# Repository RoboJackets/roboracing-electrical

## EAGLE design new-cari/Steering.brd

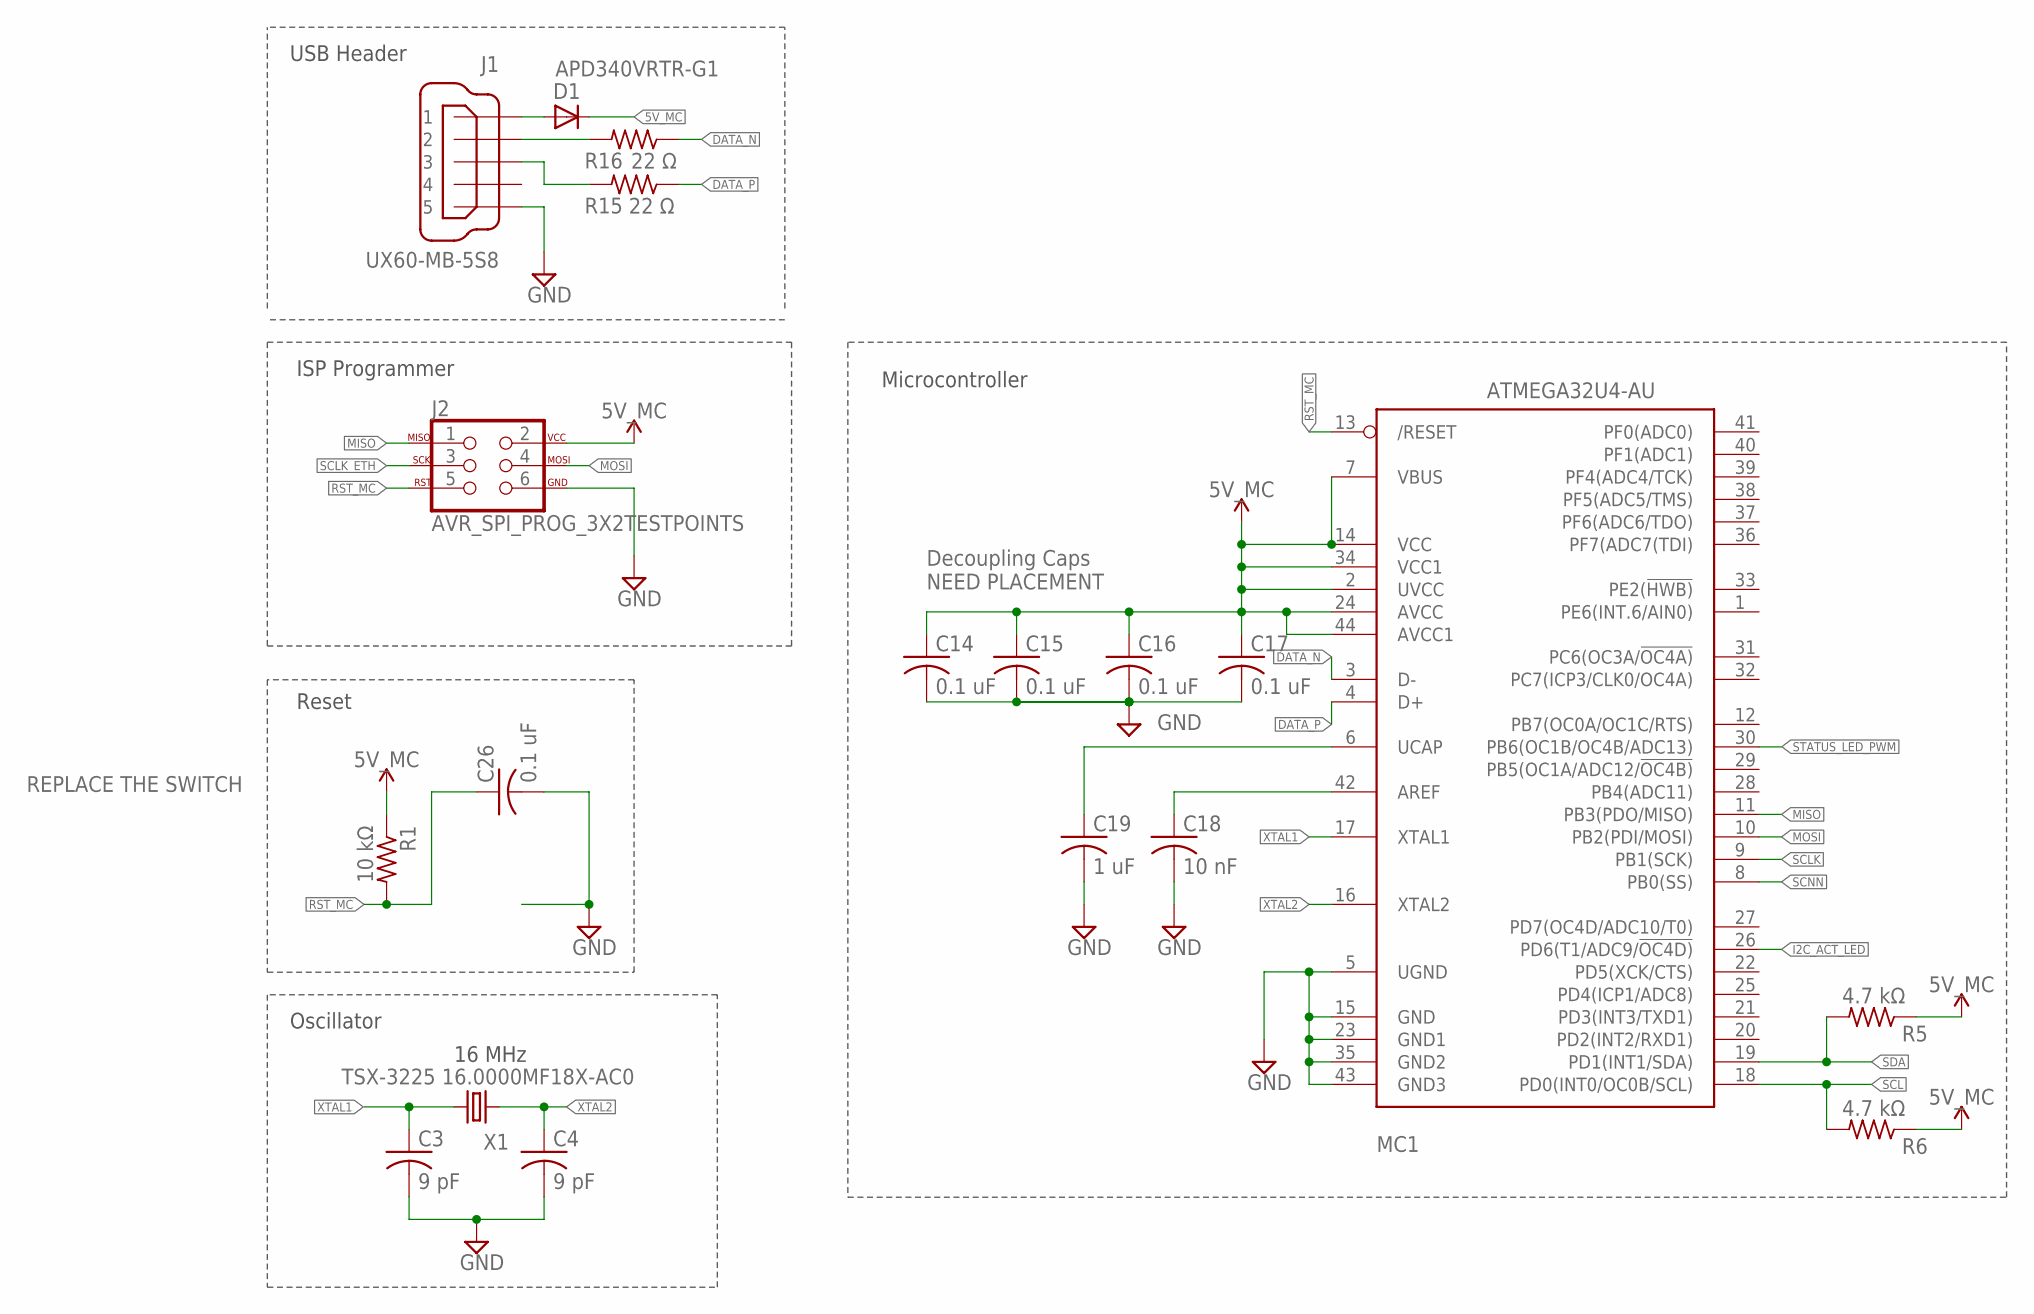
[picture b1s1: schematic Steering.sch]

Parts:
C3, C4: 9 pF; C0603
C14, C15, C16, C17, C26: 0.1 uF; C0603
C18: 10 nF; C0603
C19: 1 uF; C0603
D1: APD340VRTR-G1; DO-214AC
J1: UX60-MB-5S8
J2: AVR_SPI_PROG_3X2TESTPOINTS; 2X3_TEST_POINTS
MC1: ATMEGA32U4-AU; TQFP44
R1: 10 kΩ; R0603
R5, R6: 4.7 kΩ; R0603
R15, R16: 22 Ω; R0603
X1: TSX-3225 16.0000MF18X-AC0; XTAL-3.2X2.5

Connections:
5V_MC: C14.1, C15.1, C16.1, C17.1, D1.C, J2.2, MC1.2 (UVCC), MC1.7 (VBUS), MC1.14 (VCC), MC1.24 (AVCC), MC1.34 (VCC1), MC1.44 (AVCC1), R1.1, R5.1, R6.1
AREF: C18.1, MC1.42 (AREF)
DATA_N: MC1.3 (D-), R16.1
DATA_P: MC1.4 (D+), R15.1
GND: C3.2, C4.2, C14.2, C15.2, C16.2, C17.2, C18.2, C19.2, C26.2, J1.5, J2.6, MC1.5 (UGND), MC1.15 (GND), MC1.23 (GND1), MC1.35 (GND2), MC1.43 (GND3)
I2C_ACT_LED: MC1.26 (PD6(T1/ADC9/!OC4D))
MISO: J2.1, MC1.11 (PB3(PDO/MISO))
MOSI: J2.4, MC1.10 (PB2(PDI/MOSI))
unnamed: D1.A, J1.1
unnamed: J1.2, R16.2
unnamed: J1.3, R15.2
RST_MC: C26.1, J2.5, MC1.13 (/RESET), R1.2
SCL: MC1.18 (PD0(INT0/OC0B/SCL)), R6.2
SCLK: MC1.9 (PB1(SCK))
SCLK_ETH: J2.3
SCNN: MC1.8 (PB0(SS))
SDA: MC1.19 (PD1(INT1/SDA)), R5.2
STATUS_LED_PWM: MC1.30 (PB6(OC1B/OC4B/ADC13))
UCAP: C19.1, MC1.6 (UCAP)
XTAL1: C3.1, MC1.17 (XTAL1), X1.1
XTAL2: C4.1, MC1.16 (XTAL2), X1.3 (2)

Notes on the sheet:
Reset
Oscillator
Microcontroller
USB Header
16 MHz
ISP Programmer
Decoupling Caps NEED PLACEMENT
REPLACE THE SWITCH

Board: 2 copper layers, 19 parts (15 on the bottom side), 16 nets, no tracks yet.

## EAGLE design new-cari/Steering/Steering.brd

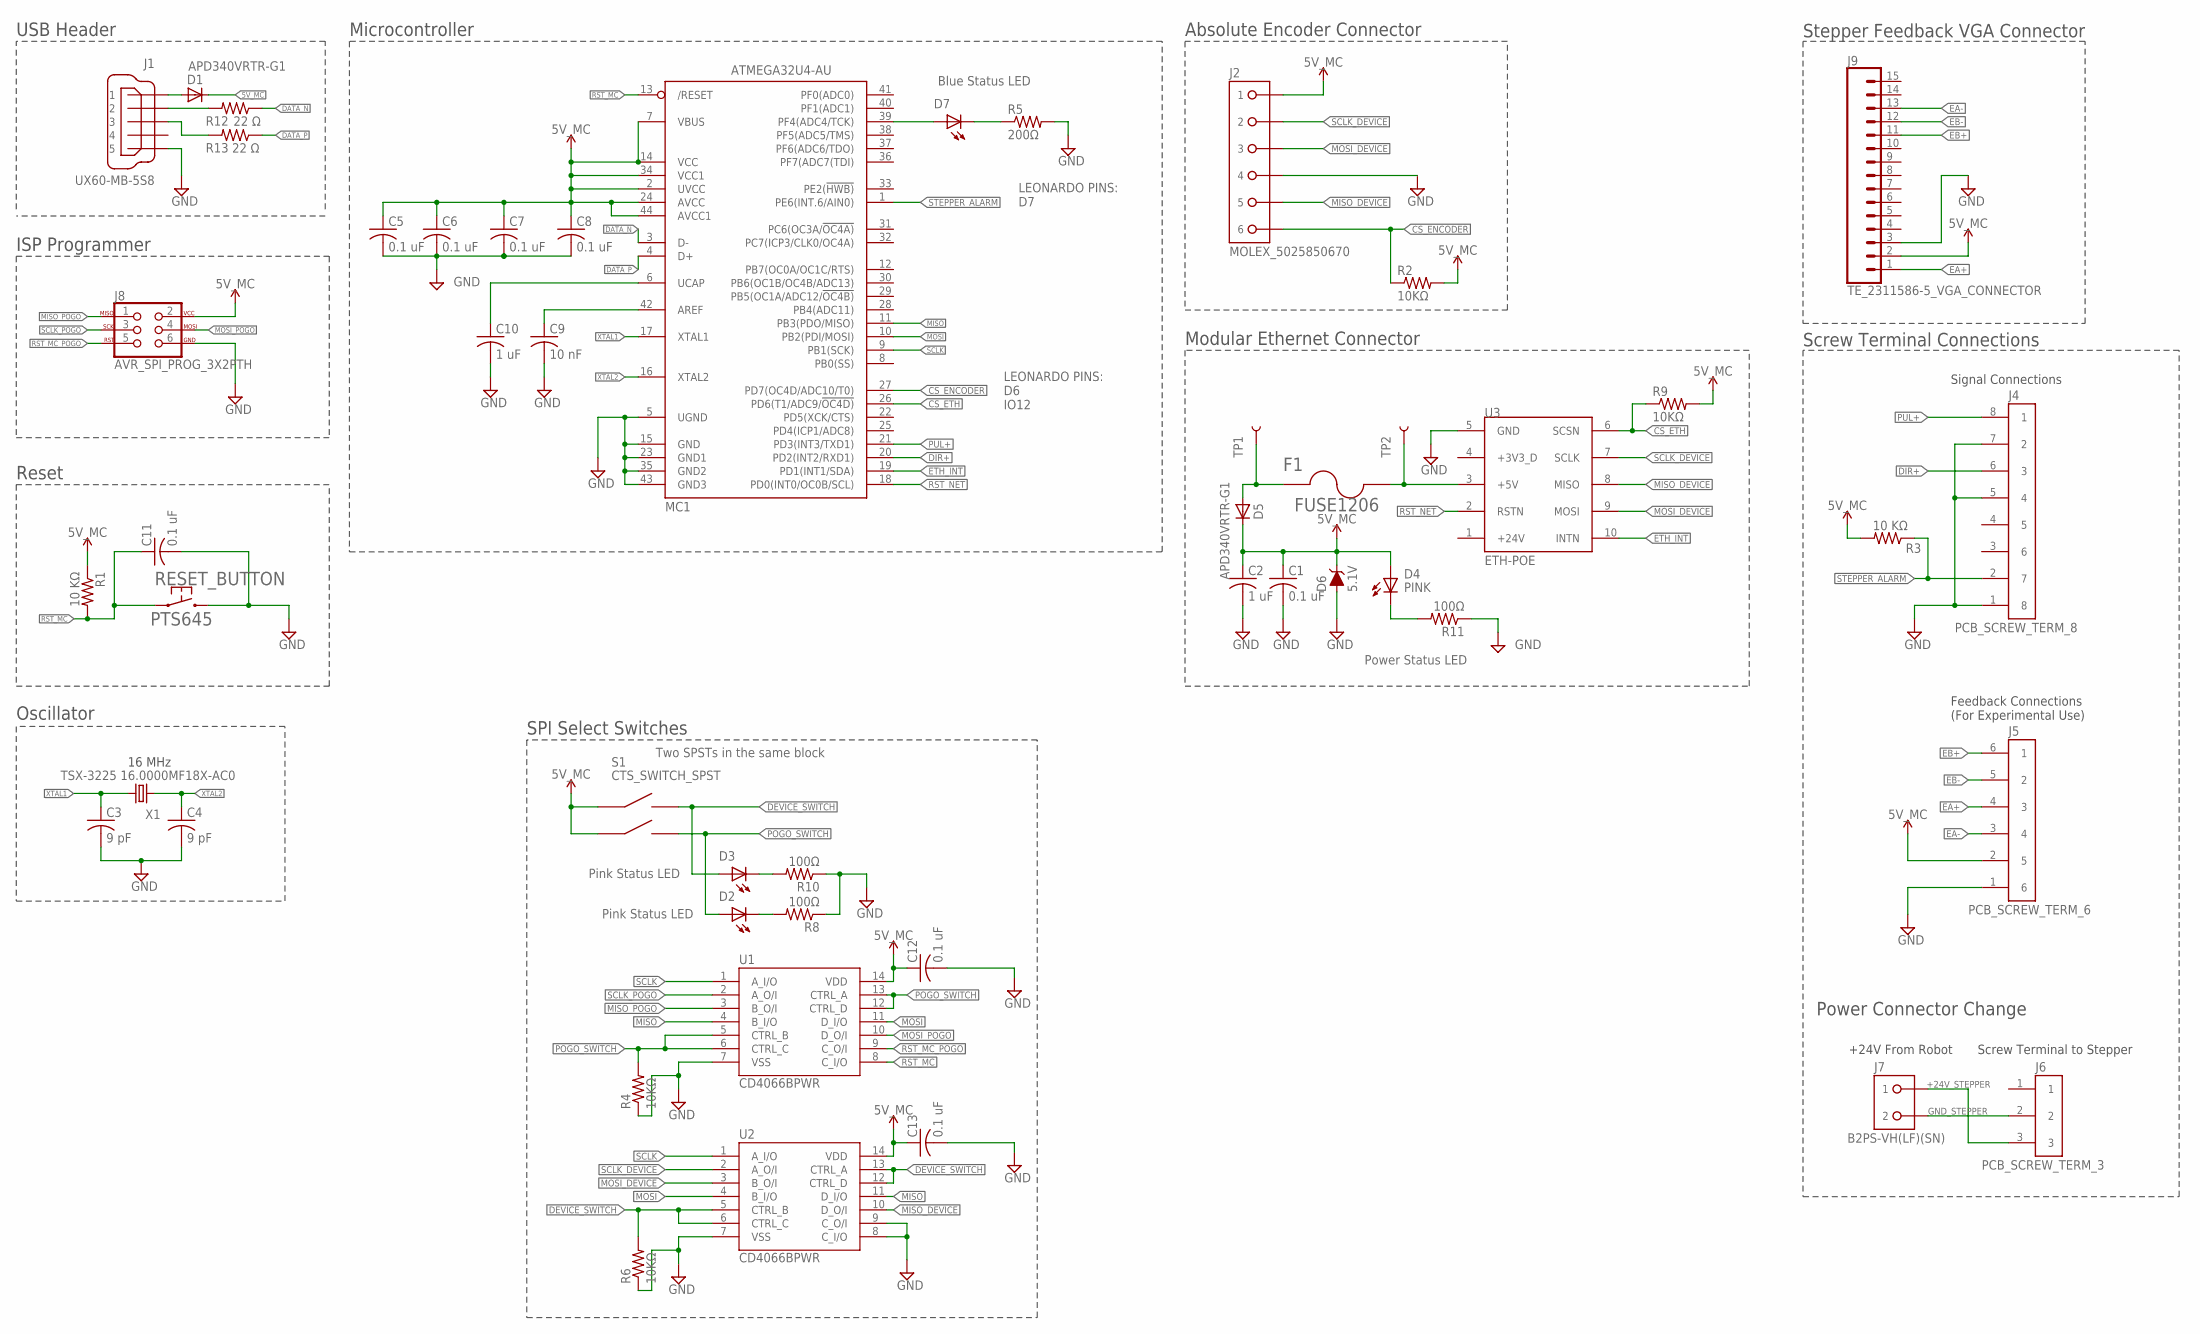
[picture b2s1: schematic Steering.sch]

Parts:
C1, C5, C6, C7, C8, C11, C12, C13: 0.1 uF; C0603
C2, C10: 1 uF; C0603
C3, C4: 9 pF; C0603
C9: 10 nF; C0603
D1, D5: APD340VRTR-G1; DO-214AC
D2, D3: LED_AA3528VRVCS/A; KINGBRIGHT_LED
D4: PINK; KINGBRIGHT_LED
D6: 5.1V; SOD-323
D7: BLUE; CHIP-LED0603
F1: FUSE1206; F1206
J1: UX60-MB-5S8
J2: MOLEX_5025850670
J4: PCB_SCREW_TERM_8; SCREW_TERMINAL_PCB_CONN_8_POLE
J5: PCB_SCREW_TERM_6; SCREW_TERMINAL_PCB_CONN_6_POLE
J6: PCB_SCREW_TERM_3; SCREW_TERMINAL_PCB_CONN_3_POLE
J7: B2PS-VH(LF)(SN); B2PS-CENTERED
J8: AVR_SPI_PROG_3X2PTH; 2X3
J9: TE_2311586-5_VGA_CONNECTOR; TE_VGA_2311586-5
MC1: ATMEGA32U4-AU; TQFP44
R1, R3: 10 KΩ; R0603
R2, R4, R6, R9: 10KΩ; R0603W
R5: 200Ω; R0603W
R8, R10, R11: 100Ω; R0603W
R12, R13: 22 Ω; R0603
RESET_BUTTON: PTS645
S1: CTS_SWITCH_SPST; CTS_DIP_SWITCH
TP1, TP2: TEST-POINTTP_15TH_THRU; TP_15TH
U1, U2: CD4066BPWR; TSSOP14
U3: ETH-POE; HDRVR10W64P4000X254_2X5_1016X508X254B
X1: TSX-3225 16.0000MF18X-AC0; XTAL-3.2X2.5

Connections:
5V_MC: C1.1, C2.1, C5.1, C6.1, C7.1, C8.1, C12.1, C13.1, D1.C, D4.P$2 (A), D5.C, D6.C, J2.1, J5.2 (5), J8.2, J9.2, MC1.2 (UVCC), MC1.7 (VBUS), MC1.14 (VCC), MC1.24 (AVCC), MC1.34 (VCC1), MC1.44 (AVCC1), R1.1, R2.2 (PIN2), R3.2, R9.2 (PIN2), S1.A2 (COMMON), S1.B2 (COMMON1), U1.14 (VDD), U2.14 (VDD)
+24V_STEPPER: J6.3, J7.1
AREF: C9.1, MC1.42 (AREF)
CS_ENCODER: J2.6, MC1.27 (PD7(OC4D/ADC10/T0)), R2.1 (PIN1)
CS_ETH: MC1.26 (PD6(T1/ADC9/!OC4D)), R9.1 (PIN1), U3.6 (SCSN)
DATA_N: MC1.3 (D-), R12.1
DATA_P: MC1.4 (D+), R13.1
DEVICE_SWITCH: D3.P$2 (A), R6.2 (PIN2), S1.A1 (A), U2.5 (CTRL_B), U2.6 (CTRL_C), U2.12 (CTRL_D), U2.13 (CTRL_A)
DIR+: J4.6 (3), MC1.20 (PD2(INT2/RXD1))
EA+: J5.4 (3), J9.1
EA-: J5.3 (4), J9.13
EB+: J5.6 (1), J9.11
EB-: J5.5 (2), J9.12
ETH_INT: MC1.19 (PD1(INT1/SDA)), U3.10 (INTN)
GND: C1.2, C2.2, C3.2, C4.2, C5.2, C6.2, C7.2, C8.2, C9.2, C10.2, C11.2, C12.2, C13.2, D6.A, J1.5, J2.4, J4.1 (8), J4.5 (4), J4.7 (2), J5.1 (6), J8.6, J9.3, MC1.5 (UGND), MC1.15 (GND), MC1.23 (GND1), MC1.35 (GND2), MC1.43 (GND3), R4.1 (PIN1), R5.2 (PIN2), R6.1 (PIN1), R8.1 (PIN1), R10.1 (PIN1), R11.1 (PIN1), RESET_BUTTON.P$3 (2), RESET_BUTTON.P$4 (2), U1.7 (VSS), U2.7 (VSS), U2.8 (C_I/O), U2.9 (C_O/I), U3.5 (GND)
GND_STEPPER: J6.2, J7.2
MISO: MC1.11 (PB3(PDO/MISO)), U1.4 (B_I/O), U2.11 (D_I/O)
MISO_DEVICE: J2.5, U2.10 (D_O/I), U3.8 (MISO)
MISO_POGO: J8.1, U1.3 (B_O/I)
MOSI: MC1.10 (PB2(PDI/MOSI)), U1.11 (D_I/O), U2.4 (B_I/O)
MOSI_DEVICE: J2.3, U2.3 (B_O/I), U3.9 (MOSI)
MOSI_POGO: J8.4, U1.10 (D_O/I)
unnamed: D1.A, J1.1
unnamed: D7.A, MC1.39 (PF4(ADC4/TCK))
unnamed: D7.C (K), R5.1 (PIN1)
unnamed: D3.P$1 (B), R10.2 (PIN2)
unnamed: D2.P$1 (B), R8.2 (PIN2)
unnamed: J1.2, R12.2
unnamed: F1.2, TP2.P$1, U3.3 (+5V)
unnamed: D4.P$1 (B), R11.2 (PIN2)
unnamed: D5.A, F1.1, TP1.P$1
unnamed: J1.3, R13.2
POGO_SWITCH: D2.P$2 (A), R4.2 (PIN2), S1.B1 (A1), U1.5 (CTRL_B), U1.6 (CTRL_C), U1.12 (CTRL_D), U1.13 (CTRL_A)
PUL+: J4.8 (1), MC1.21 (PD3(INT3/TXD1))
RST_MC: C11.1, MC1.13 (/RESET), R1.2, RESET_BUTTON.P$1 (1), RESET_BUTTON.P$2 (1), U1.8 (C_I/O)
RST_MC_POGO: J8.5, U1.9 (C_O/I)
RST_NET: MC1.18 (PD0(INT0/OC0B/SCL)), U3.2 (RSTN)
SCLK: MC1.9 (PB1(SCK)), U1.1 (A_I/O), U2.1 (A_I/O)
SCLK_DEVICE: J2.2, U2.2 (A_O/I), U3.7 (SCLK)
SCLK_POGO: J8.3, U1.2 (A_O/I)
STEPPER_ALARM: J4.2 (7), MC1.1 (PE6(INT.6/AIN0)), R3.1
UCAP: C10.1, MC1.6 (UCAP)
XTAL1: C3.1, MC1.17 (XTAL1), X1.1
XTAL2: C4.1, MC1.16 (XTAL2), X1.3 (2)

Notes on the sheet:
Reset
Oscillator
Microcontroller
USB Header
16 MHz
ISP Programmer
Stepper Feedback VGA Connector
Absolute Encoder Connector
LEONARDO PINS: D6 IO12
Screw Terminal Connections
Modular Ethernet Connector
Signal Connections
Feedback Connections (For Experimental Use)
Power Connector Change
LEONARDO PINS: D7
+24V From Robot
SPI Select Switches
Screw Terminal to Stepper
Blue Status LED
Power Status LED
Pink Status LED
Two SPSTs in the same block

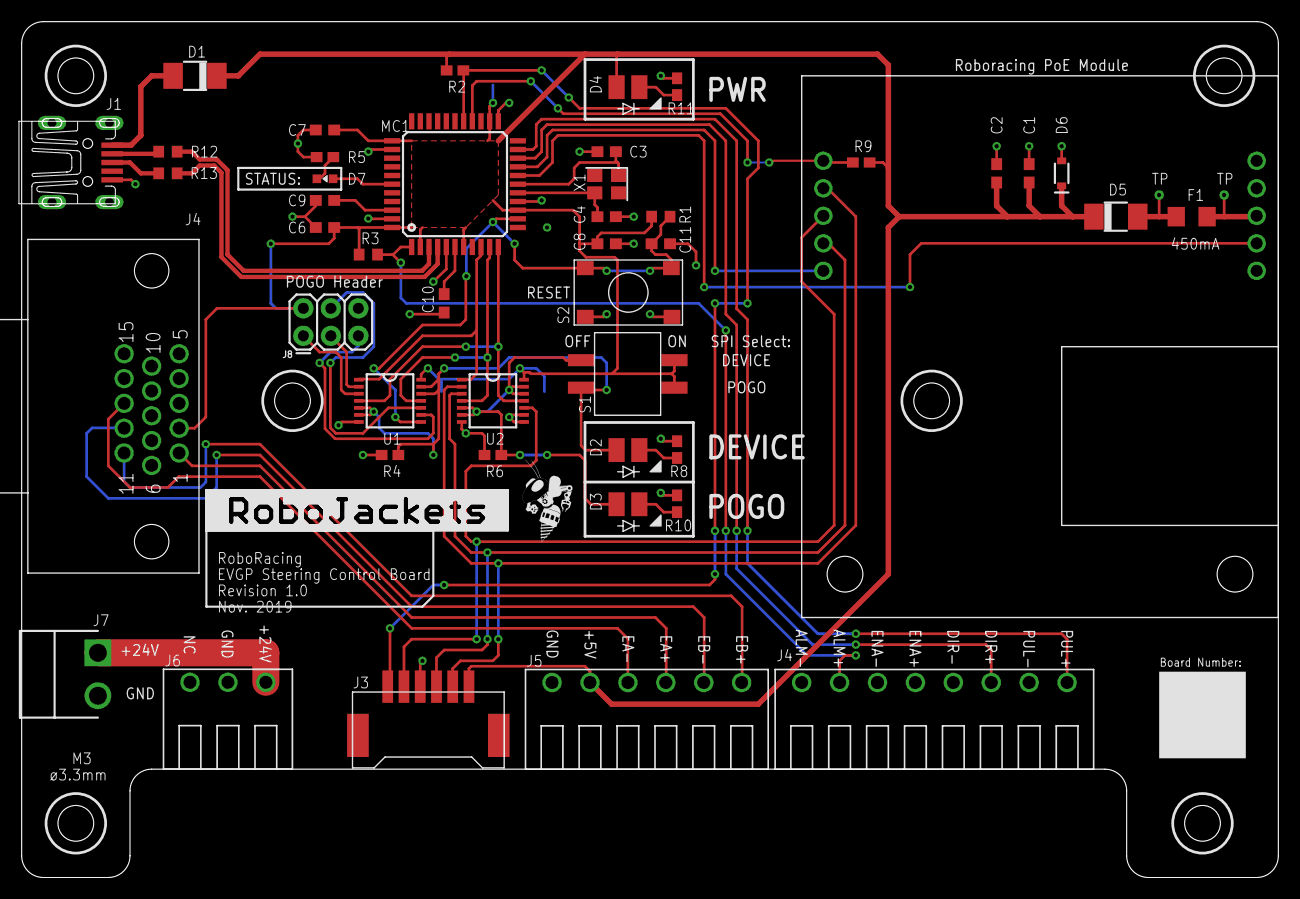
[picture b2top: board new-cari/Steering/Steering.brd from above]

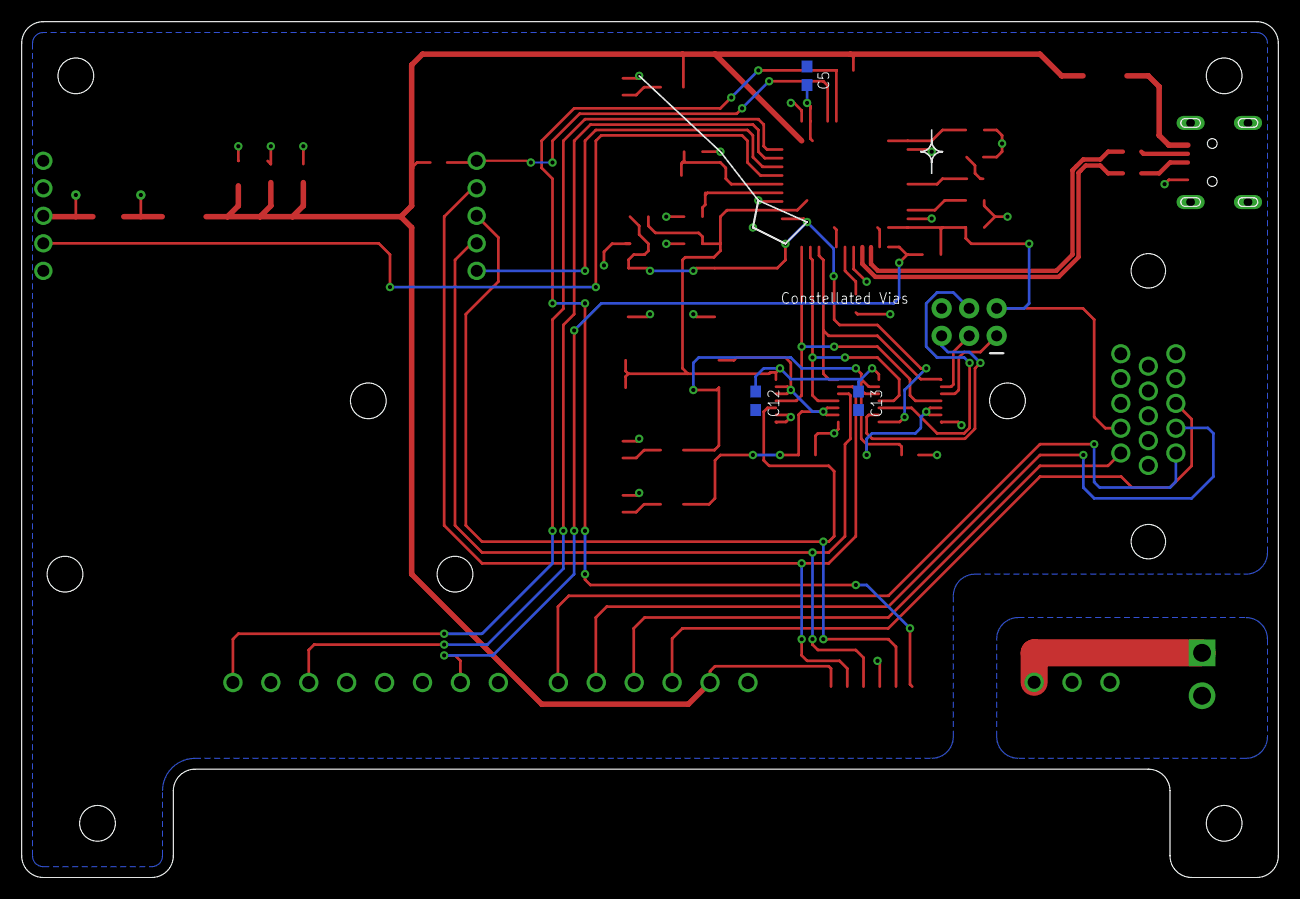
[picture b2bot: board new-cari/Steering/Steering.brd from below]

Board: 2 copper layers, 116.0 x 79.0 mm, 52 parts (3 on the bottom side), 44 nets.

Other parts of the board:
U$4: ROBOJACKETS
U$5: ROBOBUZZ_0.4X

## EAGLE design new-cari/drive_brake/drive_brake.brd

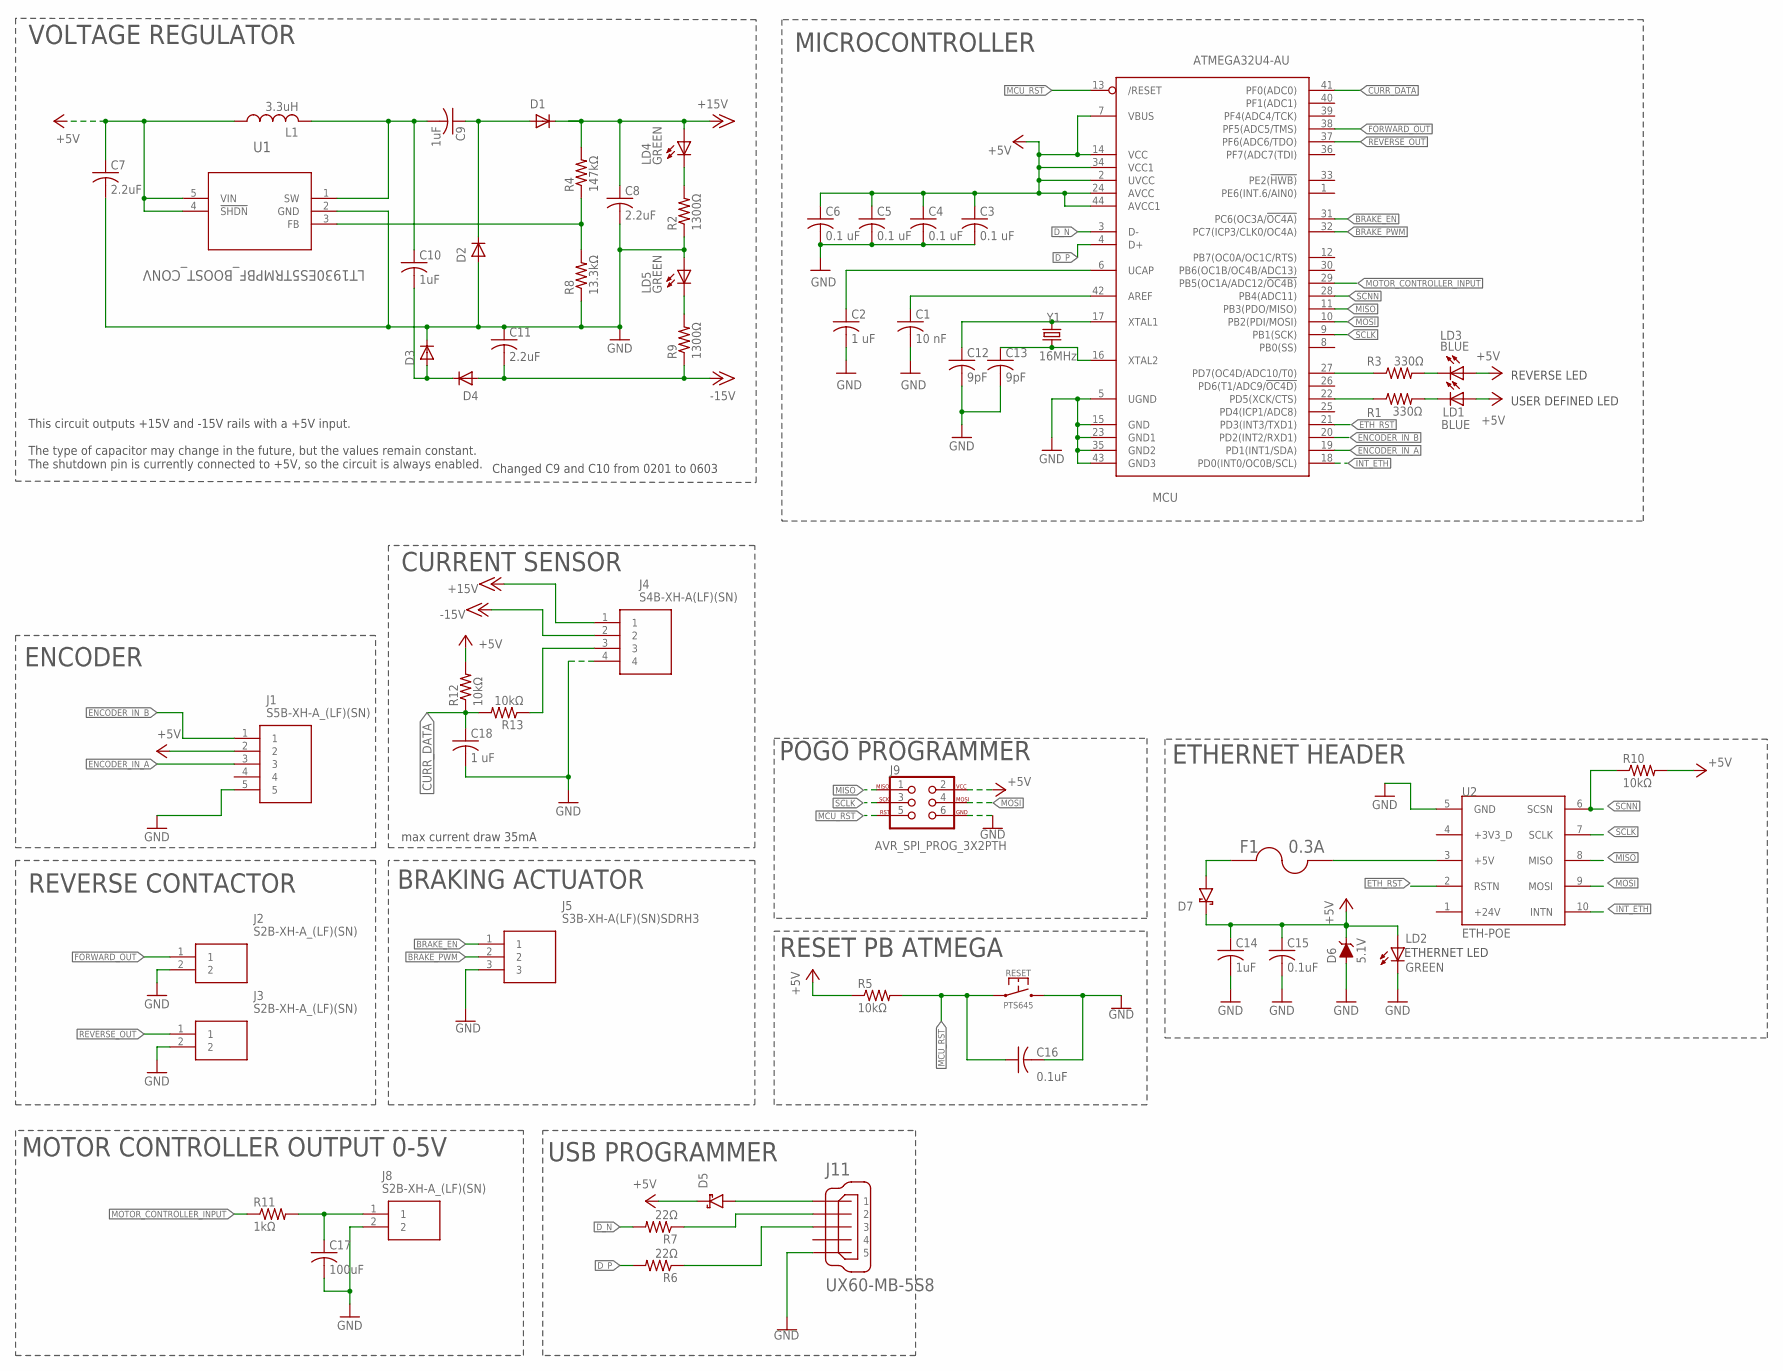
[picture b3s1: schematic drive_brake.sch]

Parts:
C1: 10 nF; C0603
C2, C18: 1 uF; C0603
C3, C4, C5, C6: 0.1 uF; C0603
C7: 2.2uF; C0805
C8, C11: 2.2uF; C1206
C9, C10, C14: 1uF; C0603
C12, C13: 9pF; C0603
C15, C16: 0.1uF; C0603
C17: 100uF; C1206
D1, D2, D3, D4: DIODE-SOD123; SOD123
D5, D7: SCHOTTKYSOD-323; SOD-323
D6: 5.1V; SOD-323
F1: 0.3A; F1206
J1: S5B-XH-A_(LF)(SN); SHDR5W80P0X250_1X5_1490X1150X6
J2, J3, J8: S2B-XH-A_(LF)(SN); SHDR2W80P0X250_1X2_740X1150X61
J4: S4B-XH-A(LF)(SN); SHDR4W64P0X250_1X4_1240X1155X7
J5: S3B-XH-A(LF)(SN)SDRH3; SHDR4
J9: AVR_SPI_PROG_3X2PTH; 2X3
J11: UX60-MB-5S8
L1: 3.3uH; L3225M
LD1, LD3: BLUE; LED-0603
LD2, LD4, LD5: GREEN; LED-0603
MCU: ATMEGA32U4-AU; TQFP44
R1, R3: 330Ω; 0603-RES
R2, R9: 1300Ω; R0603
R4: 147kΩ; R0603
R5, R10: 10kΩ; R0603
R6, R7: 22Ω; 0603-RES
R8: 13.3kΩ; R0603
R11: 1kΩ; 0603-RES
R12, R13: 10kΩ; 0603-RES
RESET: PTS645
U1: LT1930ES5TRMPBF_BOOST_CONV; SOT-5_S
U2: ETH-POE; HDRVR10W64P4000X254_2X5_1016X508X254B
Y1: 16MHz; CRYSTAL-SMD-5X3

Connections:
+5V: C3.1, C4.1, C5.1, C6.1, C7.1, C14.1, C15.1, D5.C, D6.C, D7.C, J1.2, J9.2, L1.1, LD1.A, LD2.A, LD3.A, MCU.2 (UVCC), MCU.7 (VBUS), MCU.14 (VCC), MCU.24 (AVCC), MCU.34 (VCC1), MCU.44 (AVCC1), R5.1, R10.2, R12.2, U1.4 (!SHDN), U1.5 (VIN)
+15V: C8.1, D1.C, J4.1, LD4.A, R4.2
-15V: C11.2, D4.A, J4.2, R9.1
BRAKE_EN: J5.1, MCU.31 (PC6(OC3A/!OC4A))
BRAKE_PWM: J5.2, MCU.32 (PC7(ICP3/CLK0/OC4A))
CURR_DATA: C18.1, MCU.41 (PF0(ADC0)), R12.1, R13.2
CURR_RAW: J4.3, R13.1
D_N: MCU.3 (D-), R7.2
D_P: MCU.4 (D+), R6.2
ENCODER_IN_A: J1.3, MCU.19 (PD1(INT1/SDA))
ENCODER_IN_B: J1.1, MCU.20 (PD2(INT2/RXD1))
ETH_RST: MCU.21 (PD3(INT3/TXD1)), U2.2 (RSTN)
FORWARD_OUT: J2.1, MCU.38 (PF5(ADC5/TMS))
GND: C1.2, C2.2, C3.2, C4.2, C5.2, C6.2, C7.2, C8.2, C11.1, C12.2, C13.2, C14.2, C15.2, C16.2, C17.2, C18.2, D2.A, D3.C, D6.A, J1.5, J2.2, J3.2, J4.4, J5.3, J8.2, J9.6, J11.5, LD2.C, LD5.A, MCU.5 (UGND), MCU.15 (GND), MCU.23 (GND1), MCU.35 (GND2), MCU.43 (GND3), R2.1, R8.1, RESET.P$3 (2), RESET.P$4 (2), U1.2 (GND), U2.5 (GND)
INT_ETH: MCU.18 (PD0(INT0/OC0B/SCL)), U2.10 (INTN)
MCU_RST: C16.1, J9.5, MCU.13 (/RESET), R5.2, RESET.P$1 (1), RESET.P$2 (1)
MISO: J9.1, MCU.11 (PB3(PDO/MISO)), U2.8 (MISO)
MOSI: J9.4, MCU.10 (PB2(PDI/MOSI)), U2.9 (MOSI)
MOTOR_CONTROLLER_INPUT: MCU.29 (PB5(OC1A/ADC12/!OC4B)), R11.1
unnamed: C1.1, MCU.42 (AREF)
unnamed: C2.1, MCU.6 (UCAP)
unnamed: LD3.C, R3.2
unnamed: F1.2, U2.3 (+5V)
unnamed: R4.1, R8.2, U1.3 (FB)
unnamed: C9.2, C10.1, L1.2, U1.1 (SW)
unnamed: LD1.C, R1.2
unnamed: C10.2, D3.A, D4.C
unnamed: D5.A, J11.1
unnamed: D7.A, F1.1
unnamed: J11.2, R7.1
unnamed: J11.3, R6.1
unnamed: C13.1, MCU.16 (XTAL2), Y1.1
unnamed: LD4.C, R2.2
unnamed: C12.1, MCU.17 (XTAL1), Y1.3 (2)
unnamed: C9.1, D1.A, D2.C
unnamed: LD5.C, R9.2
unnamed: C17.1, J8.1, R11.2
REVERSE_OUT: J3.1, MCU.37 (PF6(ADC6/TDO))
SCLK: J9.3, MCU.9 (PB1(SCK)), U2.7 (SCLK)
SCNN: MCU.28 (PB4(ADC11)), R10.1, U2.6 (SCSN)
TXLED: MCU.22 (PD5(XCK/CTS)), R1.1
TXLED1: MCU.27 (PD7(OC4D/ADC10/T0)), R3.1

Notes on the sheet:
This circuit outputs +15V and -15V rails with a +5V input. The type of capacitor may change in the future, but the values remain constant. The shutdown pin is currently connected to +5V, so the circuit is always enabled.
ENCODER
BRAKING ACTUATOR
REVERSE CONTACTOR
CURRENT SENSOR
USB PROGRAMMER
MOTOR CONTROLLER OUTPUT 0-5V
Changed C9 and C10 from 0201 to 0603
RESET PB ATMEGA
ETHERNET HEADER
POGO PROGRAMMER
MICROCONTROLLER
REVERSE LED
USER DEFINED LED
VOLTAGE REGULATOR
ETHERNET LED
max current draw 35mA

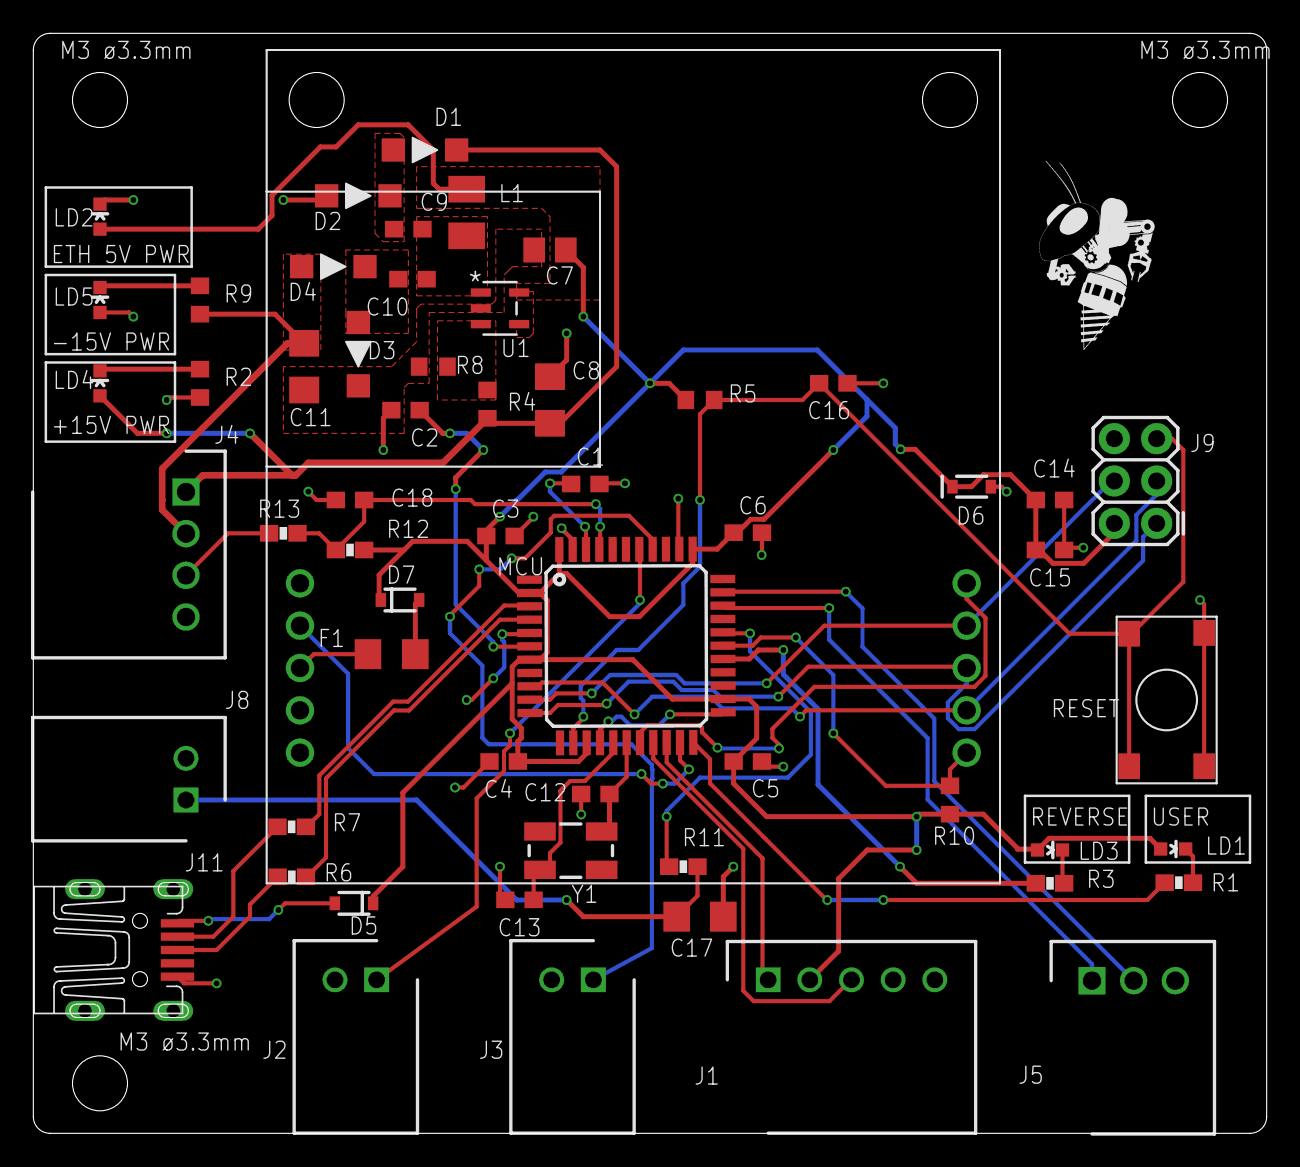
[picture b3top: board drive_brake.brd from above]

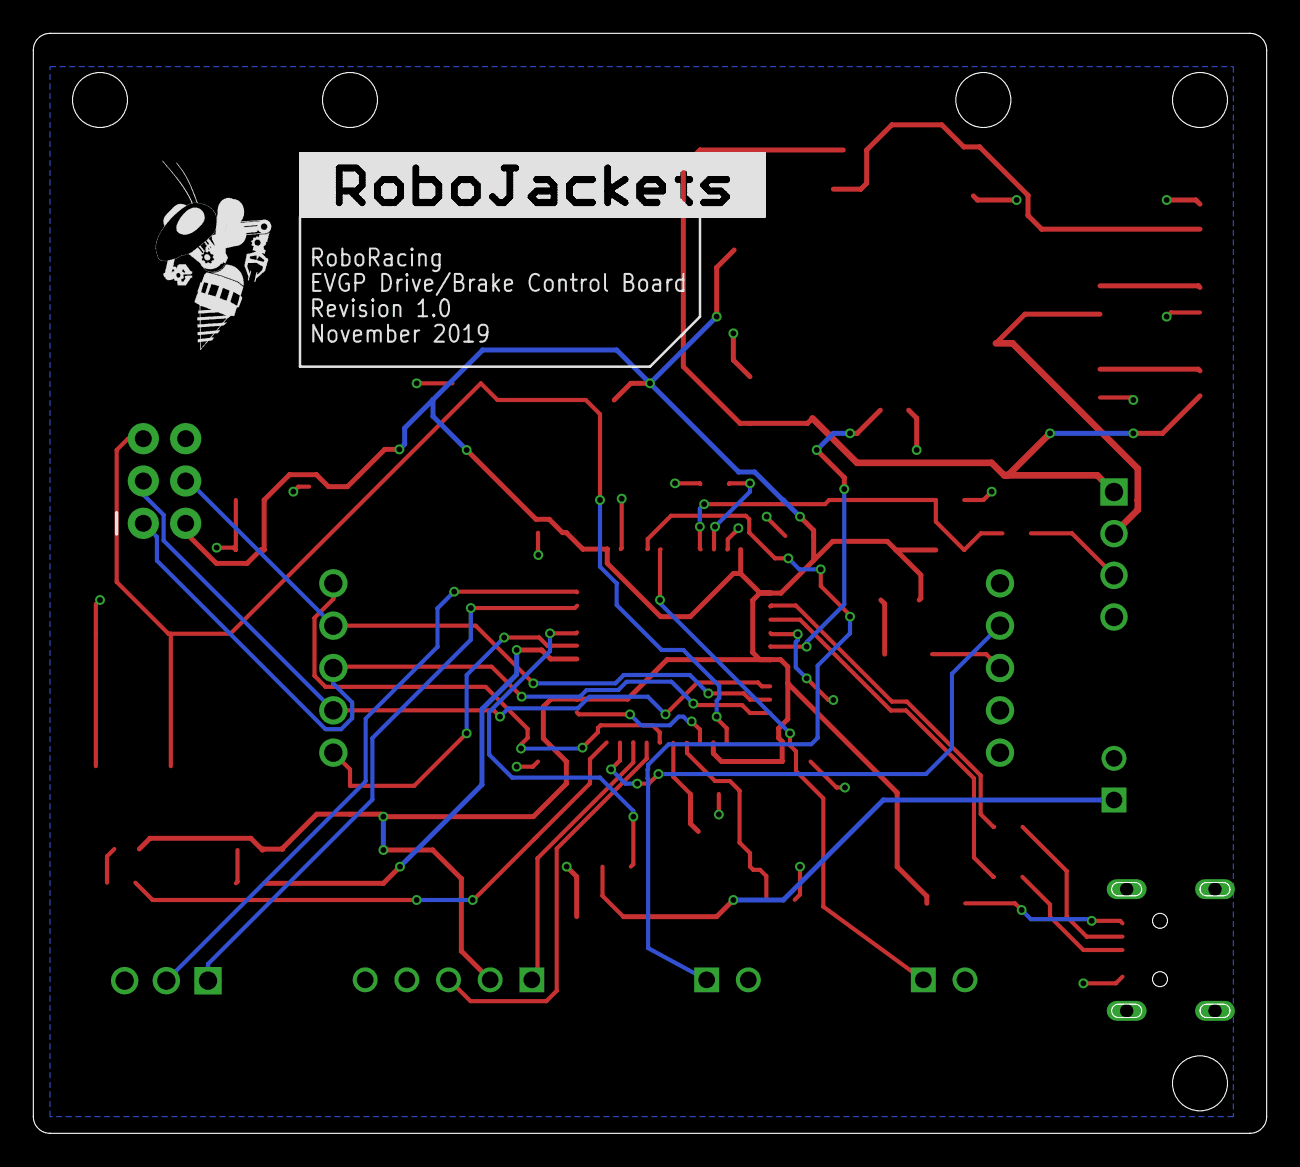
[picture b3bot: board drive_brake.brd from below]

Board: 2 copper layers, 74.0 x 66.0 mm, 61 parts (2 on the bottom side), 42 nets.

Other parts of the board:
E$3: ROBOBUZZ_0.6X
ROBORACING: ROBOJACKETS
U$1: ROBOBUZZ_0.6X

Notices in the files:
parts and their libraries:
SparkFun-Connectors: Licensing: Creative Commons ShareAlike 4.0 International - https://creativecommons.org/licenses/by-sa/4.0
COPYRIGHT: Copyright (C) 2018 Accelerated Designs. All rights reserved
